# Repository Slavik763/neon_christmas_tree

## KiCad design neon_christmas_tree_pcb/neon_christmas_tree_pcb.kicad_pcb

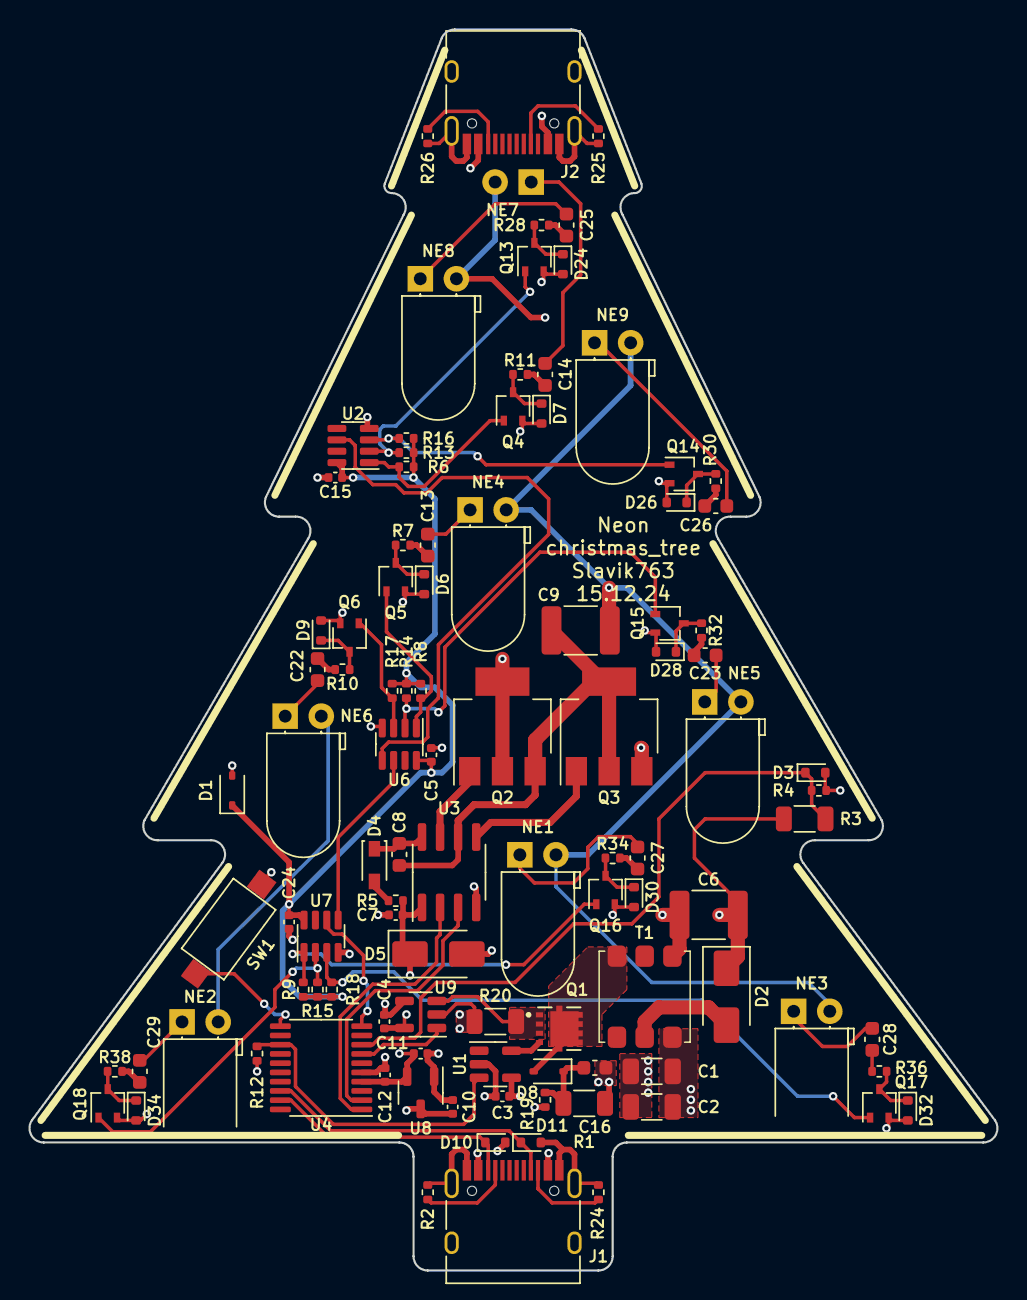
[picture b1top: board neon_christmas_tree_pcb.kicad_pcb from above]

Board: 4 copper layers, 68.0 x 87.2 mm, 103 parts (0 on the bottom side), 68 nets.

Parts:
C1, C2: 22u; C_1206_3216Metric
C3, C4, C5, C7, C12, C15, C24: 0.1u; C_0402_1005Metric
C6, C9: 1u; C_1812_4532Metric
C8, C16: 10u; C_0603_1608Metric
C10, C11: 1u; C_0402_1005Metric
C13, C14, C22, C23, C25, C26, C27, C28, C29: 10n; C_0603_1608Metric
D1: 1N4148WS; D_SOD-323
D2: US1G; D_SMA
D3, D10, D11: ESD5Zxx; D_SOD-523
D4: RRE02VSM6STR; SOD-323HE
D5: 1SMA4744A; D_SMA
D6, D7, D9, D24, D26, D28, D30, D32, D34: MM5Zxx; D_SOD-523
D8: 1N5819WS; D_SOD-323
J1, J2: USB_C_Receptacle_USB2.0; USB_C_Receptacle_HRO_TYPE-C-31-M-12
NE1, NE2, NE3, NE4, NE5, NE6, NE7, NE8, NE9: Lamp_Neon; LED_D5.0mm_Horizontal_O1.27mm_Z3.0mm
Q1: AON7292; DFN8-3x3EP_alpha_and_omega
Q2, Q3: 1N60; SOT-223-3_TabPin2
Q4, Q5, Q6, Q13, Q14, Q15, Q16, Q17, Q18: 2N7002; SOT-323_SC-70
R1: 1k; R_1206_3216Metric
R2, R4, R12, R24, R25, R26: 5.1k; R_0402_1005Metric
R3: 1M; R_1206_3216Metric
R5, R19: 10; R_0402_1005Metric
R6, R8, R9, R13, R14, R15, R16, R17, R18: 1k; R_0402_1005Metric
R7, R10, R11, R28, R30, R32, R34, R36, R38: 10k; R_0402_1005Metric
R20: 0.1; R_1206_3216Metric
SW1: SW_Push; SW_SPST_CK_RS282G05A3
T1: EE0504S
U1: MCP1416; SOT-23-5
U2, U6, U7: WS2811; FSOP8
U3: IR2101; SOIC-8_3.9x4.9mm_P1.27mm
U4: STM32C011F4Px; TSSOP-20_4.4x6.5mm_P0.65mm
U8: XC6206PxxxMR; SOT-23-3
U9: INA180A2; SOT-23-5

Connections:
+3.3V: C4.2, C11.2, C12.1, U4.4 (VDD), U8.2 (VO), U9.5 (V+)
+4V: C5.2, C15.2, C24.2, D1.1 (K), R6.2, R8.2, R9.2, R13.2, R14.2, R15.2, R16.2, R17.2, R18.2, U2.8 (VDD), U6.8 (VDD), U7.8 (VDD)
+12V: C7.2, D5.1 (K), R5.1, R19.2, U3.1 (VCC)
+200V: C6.1, D2.1 (K), Q2.2 (D), R3.2
/FLYBACK_FB: D3.1 (K), R3.1, R4.2, U4.8 (PA1)
/FLYBACK_FET_I: U4.7 (PA0), U9.1
/FLYBACK_PWM: R12.2, U1.3 (IN), U4.13 (PA6)
/SWCLK: D10.1 (K), J1.B8 (SBU2), U4.19 (PA14)
/SWDIO: D11.1 (K), J1.A8 (SBU1), U4.18 (PA13)
/Triad 1/Blue bulb/EN: Q17.1 (G), R18.1, U7.3 (OUTB)
/Triad 1/DATA_IN: U4.10 (PA3), U7.6 (DIN)
/Triad 1/DATA_OUT: U6.6 (DIN), U7.5 (DO)
/Triad 1/Green bulb/EN: Q18.1 (G), R15.1, U7.2 (OUTG)
/Triad 1/Red bulb/EN: Q16.1 (G), R9.1, U7.1 (OUTR)
/Triad 2/Blue bulb/EN: Q6.1 (G), R17.1, U6.3 (OUTB)
/Triad 2/DATA_OUT: U2.6 (DIN), U6.5 (DO)
/Triad 2/Green bulb/EN: Q15.1 (G), R14.1, U6.2 (OUTG)
/Triad 2/Red bulb/EN: Q5.1 (G), R8.1, U6.1 (OUTR)
/Triad 3/Blue bulb/EN: Q14.1 (G), R16.1, U2.3 (OUTB)
/Triad 3/Green bulb/EN: Q13.1 (G), R13.1, U2.2 (OUTG)
/Triad 3/Red bulb/EN: Q4.1 (G), R6.1, U2.1 (OUTR)
GND: C1.2, C2.2, C3.1, C4.1, C5.1, C6.2, C7.1, C10.1, C11.1, C12.2, C15.1, C24.1, D3.2 (A), D5.2 (A), D6.2 (A), D7.2 (A), D9.2 (A), D10.2 (A), D11.2 (A), D24.2 (A), D26.2 (A), D28.2 (A), D30.2 (A), D32.2 (A), D34.2 (A), J1.A1 (GND), J1.A12 (GND), J1.B1 (GND), J1.B12 (GND), J1.S1 (SHIELD), J2.A1 (GND), J2.A12 (GND), J2.B1 (GND), J2.B12 (GND), J2.S1 (SHIELD), Q3.3 (S), Q4.2 (S), Q5.2 (S), Q6.2 (S), Q13.2 (S), Q14.2 (S), Q15.2 (S), Q16.2 (S), Q17.2 (S), Q18.2 (S), R2.1, R4.1, R12.1, R20.1, R24.1, R25.1, R26.1, SW1.2, T1.6 (BA), U1.4 (GND), U2.4 (GND), U3.4 (COM), U4.5 (VSS), U6.4 (GND), U7.4 (GND), U8.1 (GND), U9.2 (GND), U9.4 (-)
unnamed: C13.1, NE4.1
unnamed: C13.2, R7.1
unnamed: C14.1, NE7.1
unnamed: C14.2, R11.1
unnamed: C22.1, NE6.1
unnamed: C22.2, R10.1
unnamed: C23.1, NE5.1
unnamed: C23.2, R32.1
unnamed: C25.1, NE8.1
unnamed: C25.2, R28.1
unnamed: C26.1, NE9.1
unnamed: C26.2, R30.1
unnamed: C27.1, NE1.1
unnamed: C27.2, R34.1
unnamed: C28.1, NE3.1
unnamed: C28.2, R36.1
unnamed: C29.1, NE2.1
unnamed: C29.2, R38.1
unnamed: D2.2 (A), T1.5 (BB)
unnamed: D4.2 (A), R5.2
unnamed: C8.2, D4.1 (K), U3.8 (VB)
unnamed: D6.1 (K), Q5.3 (D), R7.2
unnamed: D7.1 (K), Q4.3 (D), R11.2
unnamed: D8.2 (A), Q1.5 (D), T1.4 (AB)
unnamed: C16.1, D8.1 (K), R1.1, R19.1
unnamed: D9.1 (K), Q6.3 (D), R10.2
unnamed: D24.1 (K), Q13.3 (D), R28.2
unnamed: D26.1 (K), Q14.3 (D), R30.2
unnamed: D28.1 (K), Q15.3 (D), R32.2
unnamed: D30.1 (K), Q16.3 (D), R34.2
unnamed: D32.1 (K), Q17.3 (D), R36.2
unnamed: D34.1 (K), Q18.3 (D), R38.2
unnamed: J1.A5 (CC1), R2.2
unnamed: J1.B5 (CC2), R24.2
unnamed: J2.A5 (CC1), R25.2
unnamed: J2.B5 (CC2), R26.2
unnamed: Q1.4 (G), U1.5 (OUT)
unnamed: Q2.1 (G), U3.7 (HO)
unnamed: C8.1, C9.1, Q2.3 (S), Q3.2 (D), U3.6 (VS)
unnamed: Q3.1 (G), U3.5 (LO)
unnamed: SW1.1, U4.11 (PA4)
unnamed: Q1.1 (S), Q1.2 (S), Q1.3 (S), R20.2, U9.3 (+)
VBUS: C1.1, C2.1, C3.2, C10.2, C16.2, D1.2 (A), J1.A4 (VBUS), J1.A9 (VBUS), J1.B4 (VBUS), J1.B9 (VBUS), J2.A4 (VBUS), J2.A9 (VBUS), J2.B4 (VBUS), J2.B9 (VBUS), R1.2, T1.1 (AA), U1.2 (Vdd), U8.3 (VI)
VDRIVE_H: U3.2 (HIN), U4.1 (PB7)
VDRIVE_L: U3.3 (LIN), U4.2 (PC14)
Vdrive: C9.2, NE1.2, NE2.2, NE3.2, NE4.2, NE5.2, NE6.2, NE7.2, NE8.2, NE9.2

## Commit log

2024-12-29 initial
